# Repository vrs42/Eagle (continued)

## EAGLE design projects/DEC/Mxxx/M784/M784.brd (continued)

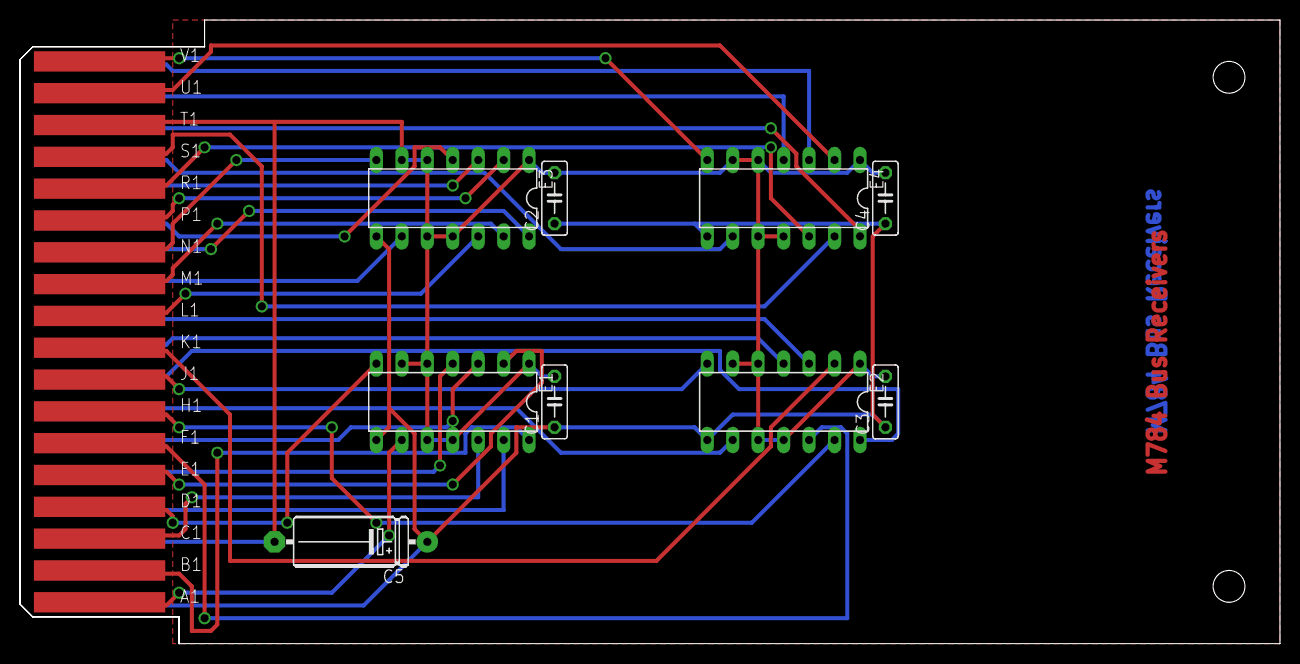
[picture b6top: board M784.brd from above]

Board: 2 copper layers, 125.7 x 62.2 mm, 11 parts (0 on the bottom side), 34 nets.
